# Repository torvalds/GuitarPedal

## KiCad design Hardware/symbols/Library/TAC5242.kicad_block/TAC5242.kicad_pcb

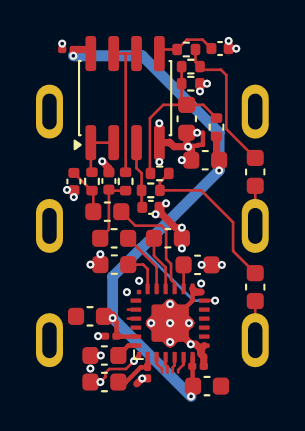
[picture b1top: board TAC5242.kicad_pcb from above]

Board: 4 copper layers, 32 parts (1 on the bottom side), 20 nets.

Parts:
C903, C904, C906, C907, C910, C911, C912, C922, C923: 2.2uF; C_0603_1608Metric
C905, C918, C919, C921: 0.1uF; C_0201_0603Metric
C908, C913: 150pF; C_0402_1005Metric
C909, C914: 2.2nF; C_0402_1005Metric
C915, C916, C917, C920: 10uF; C_0603_1608Metric
J901: AudioJack3_SwitchTR; NRJ6HM-1-PRE
R901, R902, R907, R908: 100R; R_0402_1005Metric
R903, R904, R905, R906: 1MEG; R_0402_1005Metric
U902: OPA2365AIDR; SOIC-8_3.9x4.9mm_P1.27mm
U903: TAC5242

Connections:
+3.3VA: C905.2, C915.1, C916.1, C917.1, C918.1, C919.1, R904.1, U902.8 (V+), U903.6 (IOVDD), U903.12 (MD5), U903.23 (AVDD)
/DREG: C920.1, C921.1, U903.1 (DREG)
/IN1M: C903.2, U903.16 (IN1M)
/IN1P: C907.2, U903.15 (IN1P)
/IN2M: C904.2, U903.18 (IN2M)
/IN2P: C912.2, U903.17 (IN2P)
/IN^{LEFT}: C906.1, J901.T
/IN^{RIGHT}: C911.1, J901.R
/MICBIAS: C923.1, U903.14 (MICBIAS)
/VREF: C922.1, U903.24 (VREF)
GND: C903.1, C904.1, C905.1, C908.2, C909.1, C910.1, C913.2, C914.1, C915.2, C916.2, C917.2, C918.2, C919.2, C920.2, C921.2, C922.2, C923.2, J901.RN, J901.S, J901.TN, R905.2, U902.4 (V-), U903.7 (MD1), U903.8 (MD2), U903.9 (MD3), U903.10 (MD4), U903.13 (MD0), U903.A1 (GND), U903.A2 (GND), U903.A3 (GND), U903.A4 (GND), U903.PAD (GND)
unnamed: C906.2, R901.1, R903.2
unnamed: C907.1, C909.2, R902.2
unnamed: C910.2, R903.1, R904.2, R905.1, R906.2
unnamed: C911.2, R906.1, R907.1
unnamed: C912.1, C914.2, R908.2
unnamed: C908.1, R901.2, U902.3 (+)
unnamed: R902.1, U902.1, U902.2 (-)
unnamed: C913.1, R907.2, U902.5 (+)
unnamed: R908.1, U902.6 (-), U902.7

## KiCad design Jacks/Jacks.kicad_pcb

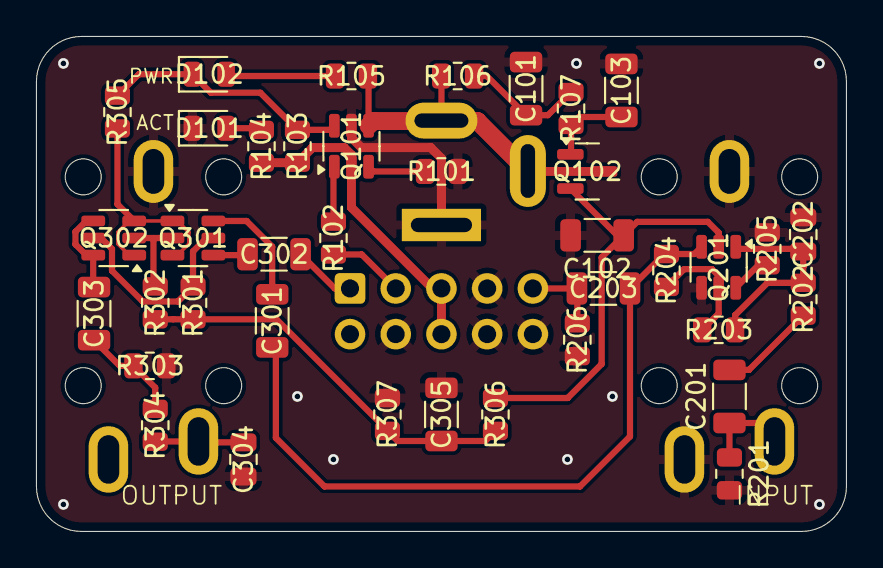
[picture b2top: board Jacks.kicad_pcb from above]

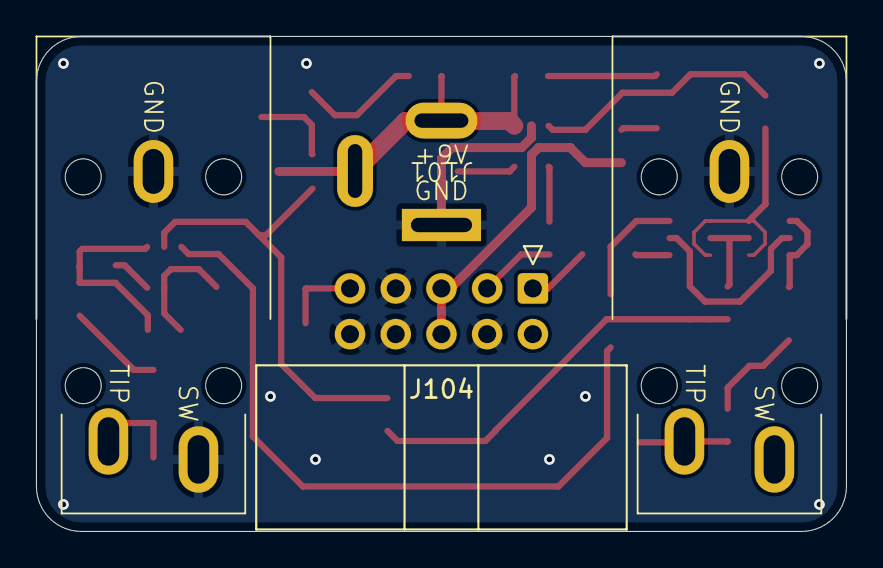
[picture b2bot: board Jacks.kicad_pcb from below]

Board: 2 copper layers, 45.0 x 27.5 mm, 44 parts (4 on the bottom side), 29 nets.

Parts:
Box101: 125B
Box102: 1590B
C101, C102, C103, C305: 10uF; C_1206_3216Metric
C201, C203: 4.7uF; C_1206_3216Metric
C202: 150pF; C_0805_2012Metric
C301, C302, C303: 1uF; C_1206_3216Metric
C304: 220pF; C_0805_2012Metric
D101, D102: LED; LED_0805_2012Metric
J101: Barrel_Jack_Switch; Wurth WR-DC 2.1mm Power Jack
J102, J103: AudioJack2_Ground; CK-6.35
J104: Conn_02x05_Odd_Even; IDC-Header_2x05_P2.54mm_Horizontal
Q101, Q301, Q302: DMC3071LVT; TSOT-23-6
Q102: BC846; SOT-23
Q201: LS844; SOT-23-6
R101, R102, R103: 100k; R_0805_2012Metric
R104, R105, R106, R107, R304: 2k2; R_0805_2012Metric
R201, R203, R206, R301, R302, R303: 1MEG; R_0805_2012Metric
R202: 1k; R_0805_2012Metric
R204, R205: 1k5; R_0805_2012Metric
R305: 10MEG; R_0805_2012Metric
R306, R307: 4k7; R_0805_2012Metric

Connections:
+VA: C102.1, Q102.2 (E), Q201.2 (D), R306.2
BUFFERED: C203.1, C301.1, Q201.3 (S), R204.1
GATE: Q301.1 (G), Q301.3 (G), Q302.1 (G), Q302.3 (G), R305.2
GND: C101.2, C102.2, C103.2, C202.2, C304.2, C305.1, D101.1 (K), J101.1, J102.G, J102.S, J103.G, J104.4, J104.7, J104.8, J104.10, Q101.5 (S), Q201.4 (G), R101.2, R201.2, R205.2, R206.2, R303.1, R307.1
IN^{CONN}: C201.1, J102.T, R201.1
IN^{EFF}: C203.2, J104.9, R206.1
unnamed: C101.1, R106.2, R107.1
unnamed: C201.2, R202.1
unnamed: C303.2, R303.2, R304.1
unnamed: D101.2 (A), R104.2
unnamed: D102.2 (A), R105.2
unnamed: Q101.1 (G), R102.2
unnamed: Q101.3 (G), R101.1
unnamed: C103.1, Q102.1 (B), R107.2
unnamed: C202.1, Q201.1 (G), R202.2, R203.1
unnamed: Q201.5 (D), R203.2, R204.2
unnamed: Q201.6 (S), R205.1
unnamed: C301.2, Q301.6 (D)
unnamed: Q301.5 (S), Q302.5 (S), R301.1
unnamed: C302.2, Q301.4 (D)
unnamed: Q301.2 (S), Q302.2 (S), R302.2
unnamed: C303.1, Q302.4 (D), Q302.6 (D)
ON_LOW: D102.1 (K), Q101.6 (D), R103.2, R305.1
ON_OFF: J104.3, R102.1
OUT^{CONN}: C304.1, J103.T, R304.2
OUT^{EFF}: C302.1, J104.1
PWRIN: J101.2, J101.3, Q101.4 (D), Q102.3 (C), R105.1, R106.1
VBIAS: C305.2, R301.2, R302.1, R306.1, R307.2
VIN: J104.5, J104.6, Q101.2 (S), R103.1, R104.1

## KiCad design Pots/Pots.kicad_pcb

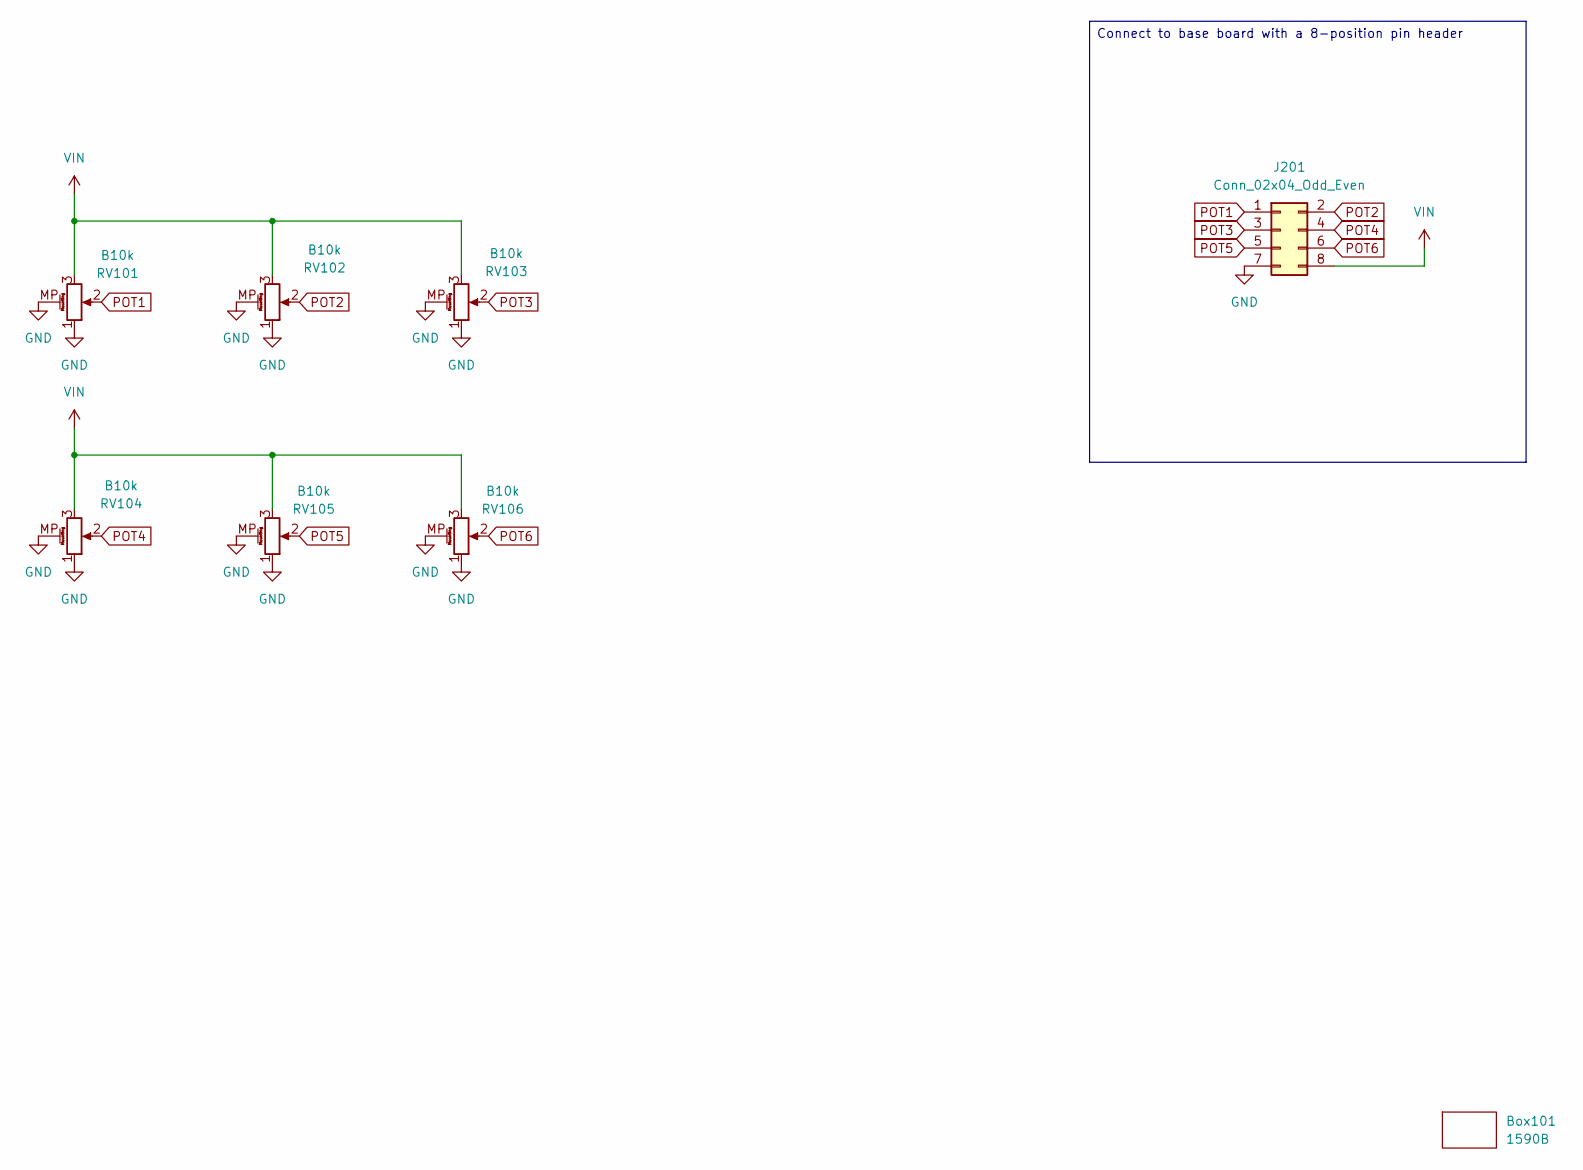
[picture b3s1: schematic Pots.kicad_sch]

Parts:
Box101: 1590B
J201: Conn_02x04_Odd_Even; PinSocket_2x04_P2.54mm_Vertical
RV101, RV102, RV103, RV104, RV105, RV106: B10k; Potentiometer_9mm_MP_Low_profile

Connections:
GND: J201.7, RV101.1, RV101.MP (MountPin), RV102.1, RV102.MP (MountPin), RV103.1, RV103.MP (MountPin), RV104.1, RV104.MP (MountPin), RV105.1, RV105.MP (MountPin), RV106.1, RV106.MP (MountPin)
POT1: J201.1, RV101.2
POT2: J201.2, RV102.2
POT3: J201.3, RV103.2
POT4: J201.4, RV104.2
POT5: J201.5, RV105.2
POT6: J201.6, RV106.2
VIN: J201.8, RV101.3, RV102.3, RV103.3, RV104.3, RV105.3, RV106.3

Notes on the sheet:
Connect to base board with a 8-position pin header

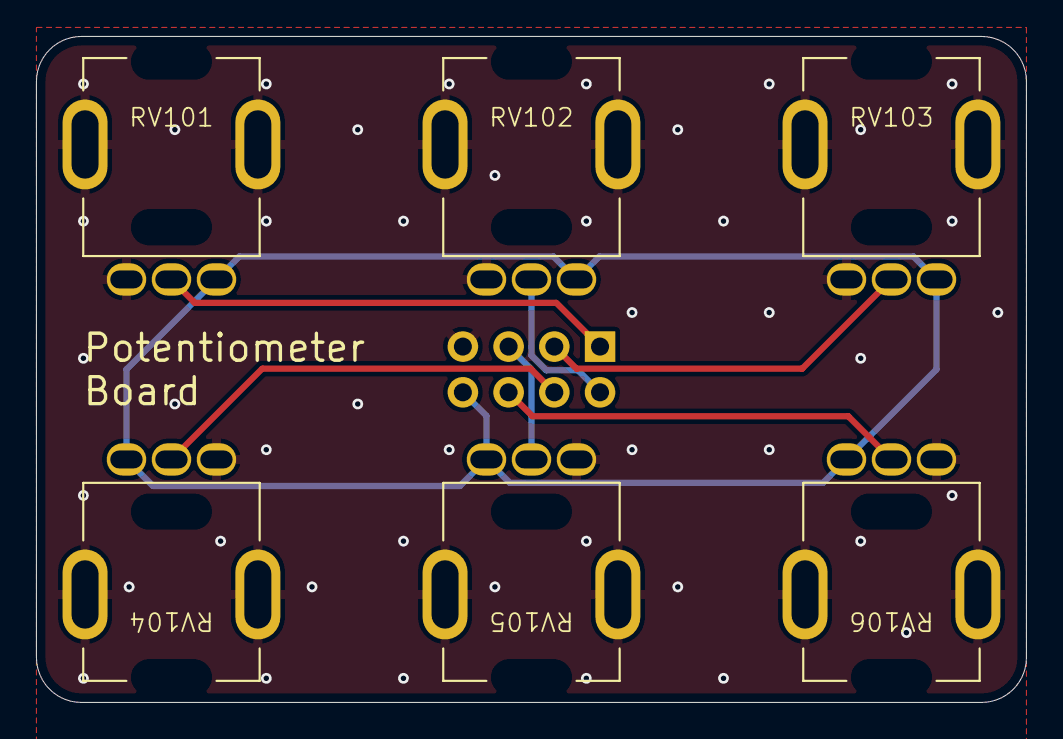
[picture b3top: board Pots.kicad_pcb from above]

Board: 2 copper layers, 55.0 x 37.0 mm, 8 parts (1 on the bottom side), 8 nets.

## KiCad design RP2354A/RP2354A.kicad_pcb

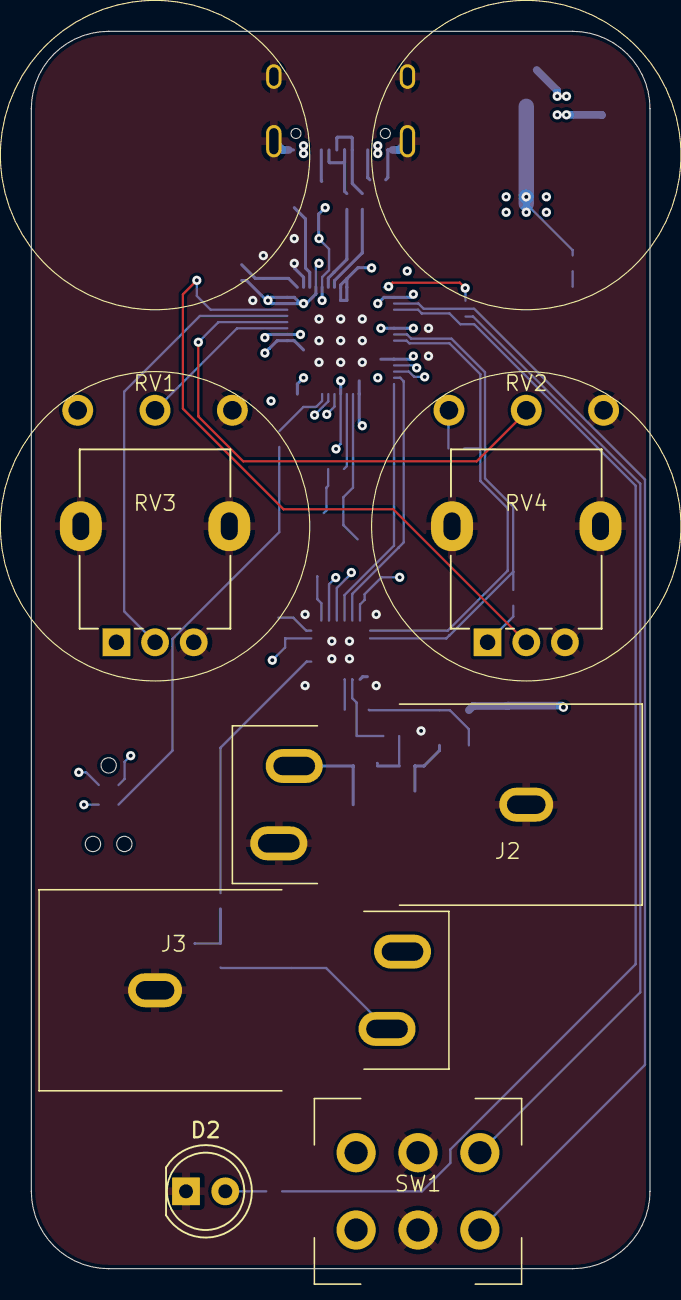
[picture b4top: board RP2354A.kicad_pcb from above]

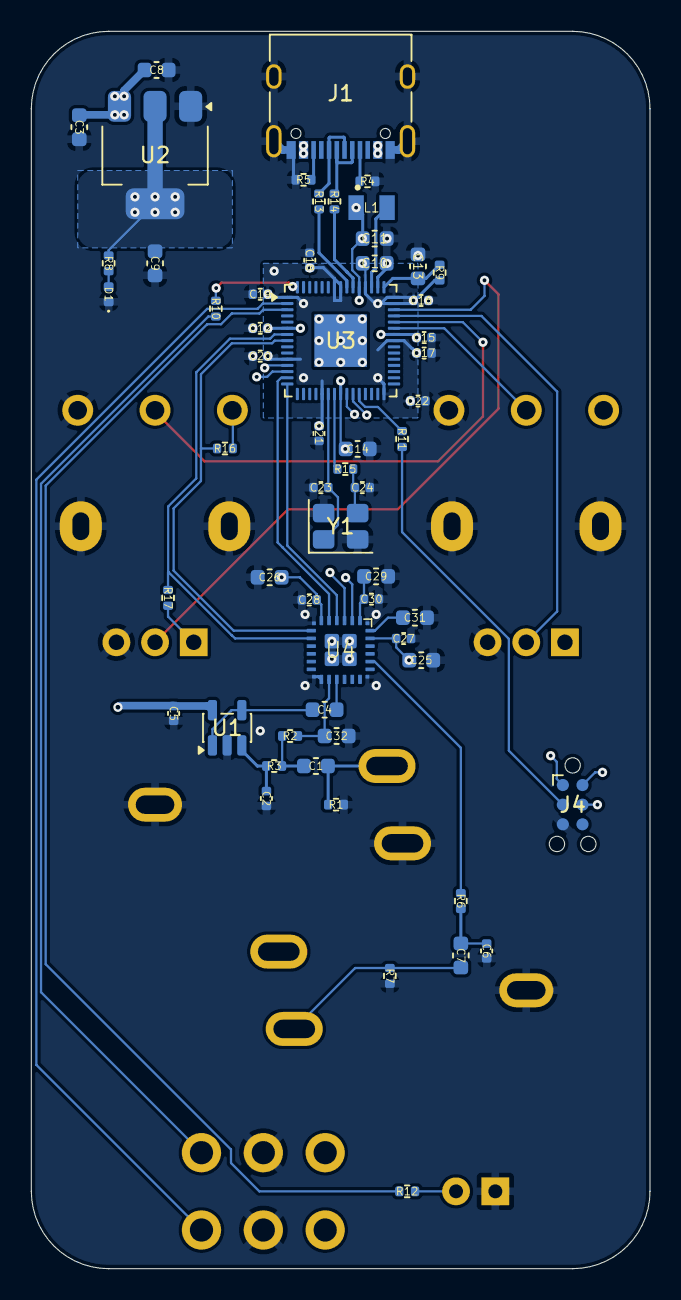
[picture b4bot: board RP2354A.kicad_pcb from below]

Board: 6 copper layers, 40.0 x 80.0 mm, 66 parts (58 on the bottom side), 46 nets.

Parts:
C1, C4, C7, C31, C32: 1uF; C_0603_1608Metric
C2, C6: 150pF; C_0402_1005Metric
C3, C8, C9, C25, C26, C29: 10uF; C_0603_1608Metric
C5, C12, C15, C16, C17, C18, C19, C20, C21, C22, C27, C28, C30: 0.1uF; C_0402_1005Metric
C10, C11, C13, C14: 4.7uF; C_0603_1608Metric
C23, C24: 15pF; C_0402_1005Metric
D1: LED; LED_0402_1005Metric
D2: LED; LED_D5.0mm
J1: TYPE-C16PIN; USB_C_Receptacle_XKB_U262-16XN-4BVC11
J2, J3: AudioJack2_SwitchT; CK-6.35-no-NPTH
J4: TC2030-NL; Tag-Connect_TC2030-IDC-NL_2x03_P1.27mm_Vertical
L1: 3.3uH; AOTA-B2016
R1, R2, R7: 1MEG; R_0402_1005Metric
R3, R6, R8, R10, R11, R12, R15: 1k; R_0402_1005Metric
R4, R5, R16, R17: 5k1; R_0402_1005Metric
R9, R13, R14: 33R; R_0402_1005Metric
RV1, RV2: 10k; Potentiometer-Basic
RV3, RV4: 10k; Potentiometer_9mm_MP
SW1: SW_Push_DPDT; FS5700DPMT2B2M2QE
U1: OPA365xxDBV; SOT-23-5
U2: NCP1117-3.3_SOT223; SOT-223-3_TabPin2
U3: RP2354A; QFN-60-1EP_7x7mm_P0.4mm_EP3.4x3.4mm
U4: TAC5112
Y1: ABM8-272-T3; Crystal_SMD_3225-4Pin_3.2x2.5mm

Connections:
+1V1: C11.1, C12.1, C14.1, C15.1, L1.1, U3.6 (DVDD), U3.23 (DVDD), U3.39 (DVDD), U3.50 (VREG_FB)
+3V3: C9.1, C10.1, C16.1, C17.1, C18.1, C19.1, C20.1, C21.1, C22.1, C25.1, C26.1, C27.1, C28.1, J4.1 (VCC), R8.1, R9.1, R16.1, R17.1, RV1.1, RV2.1, RV3.1, RV4.1, U2.2 (VO), U3.1 (IOVDD), U3.11 (IOVDD), U3.20 (IOVDD), U3.30 (IOVDD), U3.38 (IOVDD), U3.44 (ADC_AVDD), U3.45 (IOVDD), U3.49 (VREG_VIN), U3.53 (USB_OTP_VDD), U3.54 (QSPI_IOVDD), U4.6 (IOVDD), U4.23 (AVDD)
/RPi/BOOTSEL: R10.1, SW1.3 (C)
/RPi/LED: R12.2, U3.3 (GPIO1)
/RPi/NRST: J4.3 (~RESET), R11.1
/RPi/STOMP: SW1.6 (C), U3.2 (GPIO0)
/RPi/VREG_AVDD: C13.1, R9.2, U3.46 (VREG_AVDD)
/RPi/VREG_LX: L1.2, U3.48 (VREG_LX)
/RPi/XIN: C23.1, U3.21 (XIN), Y1.1
/RPi/XOUT: R15.1, U3.22 (XOUT)
BCLK: U3.12 (GPIO8), U4.2 (BCLK)
DIN: U3.14 (GPIO10), U4.5 (DIN)
DOUT: U3.15 (GPIO11), U4.4 (DOUT)
DREG: C29.1, C30.1, U4.1 (DREG)
FSYNC: U3.13 (GPIO9), U4.3 (FSYNC)
GND: C2.2, C3.1, C5.1, C6.1, C8.2, C9.2, C10.2, C11.2, C12.2, C13.2, C14.2, C15.2, C16.2, C17.2, C18.2, C19.2, C20.2, C21.2, C22.2, C23.2, C24.2, C25.2, C26.2, C27.2, C28.2, C29.2, C30.2, C31.2, C32.2, D1.1 (K), D2.1 (K), J1.A1 (GND), J1.A12 (GND), J1.B1 (GND), J1.B12 (GND), J1.S1 (SHIELD), J2.S, J2.TN, J3.S, J4.5 (GND), R1.2, R4.2, R5.2, R7.2, RV1.3, RV2.3, RV3.3, RV3.MP (MountPin), RV4.3, RV4.MP (MountPin), SW1.2 (B), SW1.5 (B), U1.2 (V-), U2.1 (GND), U3.47 (VREG_PGND), U3.61 (GND), U4.13 (ADDR), U4.A1 (GND), U4.A2 (GND), U4.A3 (GND), U4.A4 (GND), U4.PAD (GND), Y1.2, Y1.4
IN^{CONN}: C1.1, J2.T, R1.1
IN^{EFF}: C4.2, U4.15 (IN1P)
unnamed: C1.2, R2.2, R3.1
unnamed: C6.2, C7.1, R6.2
unnamed: C24.1, R15.2, Y1.3
unnamed: D1.2 (A), R8.2
unnamed: D2.2 (A), R12.1
unnamed: J1.A5 (CC1), R4.1
unnamed: J1.B5 (CC2), R5.1
unnamed: J4.4 (SWCLK), U3.24 (SWCLK)
unnamed: J4.2 (SWDIO), U3.25 (SWD)
unnamed: C2.1, R3.2, U1.3 (+)
unnamed: C4.1, U1.1, U1.4 (-)
unnamed: R10.2, U3.60 (QSPI_SS)
unnamed: R11.2, U3.26 (RUN)
unnamed: R14.1, U3.51 (USB_DM)
unnamed: R13.1, U3.52 (USB_DP)
OUT^{CONN}: C7.2, J3.T, R7.1
OUT^{EFF}: R6.1, U4.20 (OUT1P)
POT1: RV1.2, U3.40 (GPIO26_ADC0)
POT2: RV2.2, U3.41 (GPIO27_ADC1)
POT3: RV3.2, U3.42 (GPIO28_ADC2)
POT4: RV4.2, U3.43 (GPIO29_ADC3)
SCL: R16.2, U3.8 (GPIO5), U4.7 (SCL)
SDA: R17.2, U3.7 (GPIO4), U4.8 (SDA)
USB_D+: J1.A6 (D+), J1.B6 (D+), R13.2
USB_D-: J1.A7 (D-), J1.B7 (D-), R14.2
VBIAS: C32.1, R2.1, U4.14 (MICBIAS)
VBUS: C3.2, C5.2, C8.1, J1.A4 (VBUS), J1.A9 (VBUS), J1.B4 (VBUS), J1.B9 (VBUS), U1.5 (V+), U2.3 (VI)
VREF: C31.1, U4.24 (VREF)

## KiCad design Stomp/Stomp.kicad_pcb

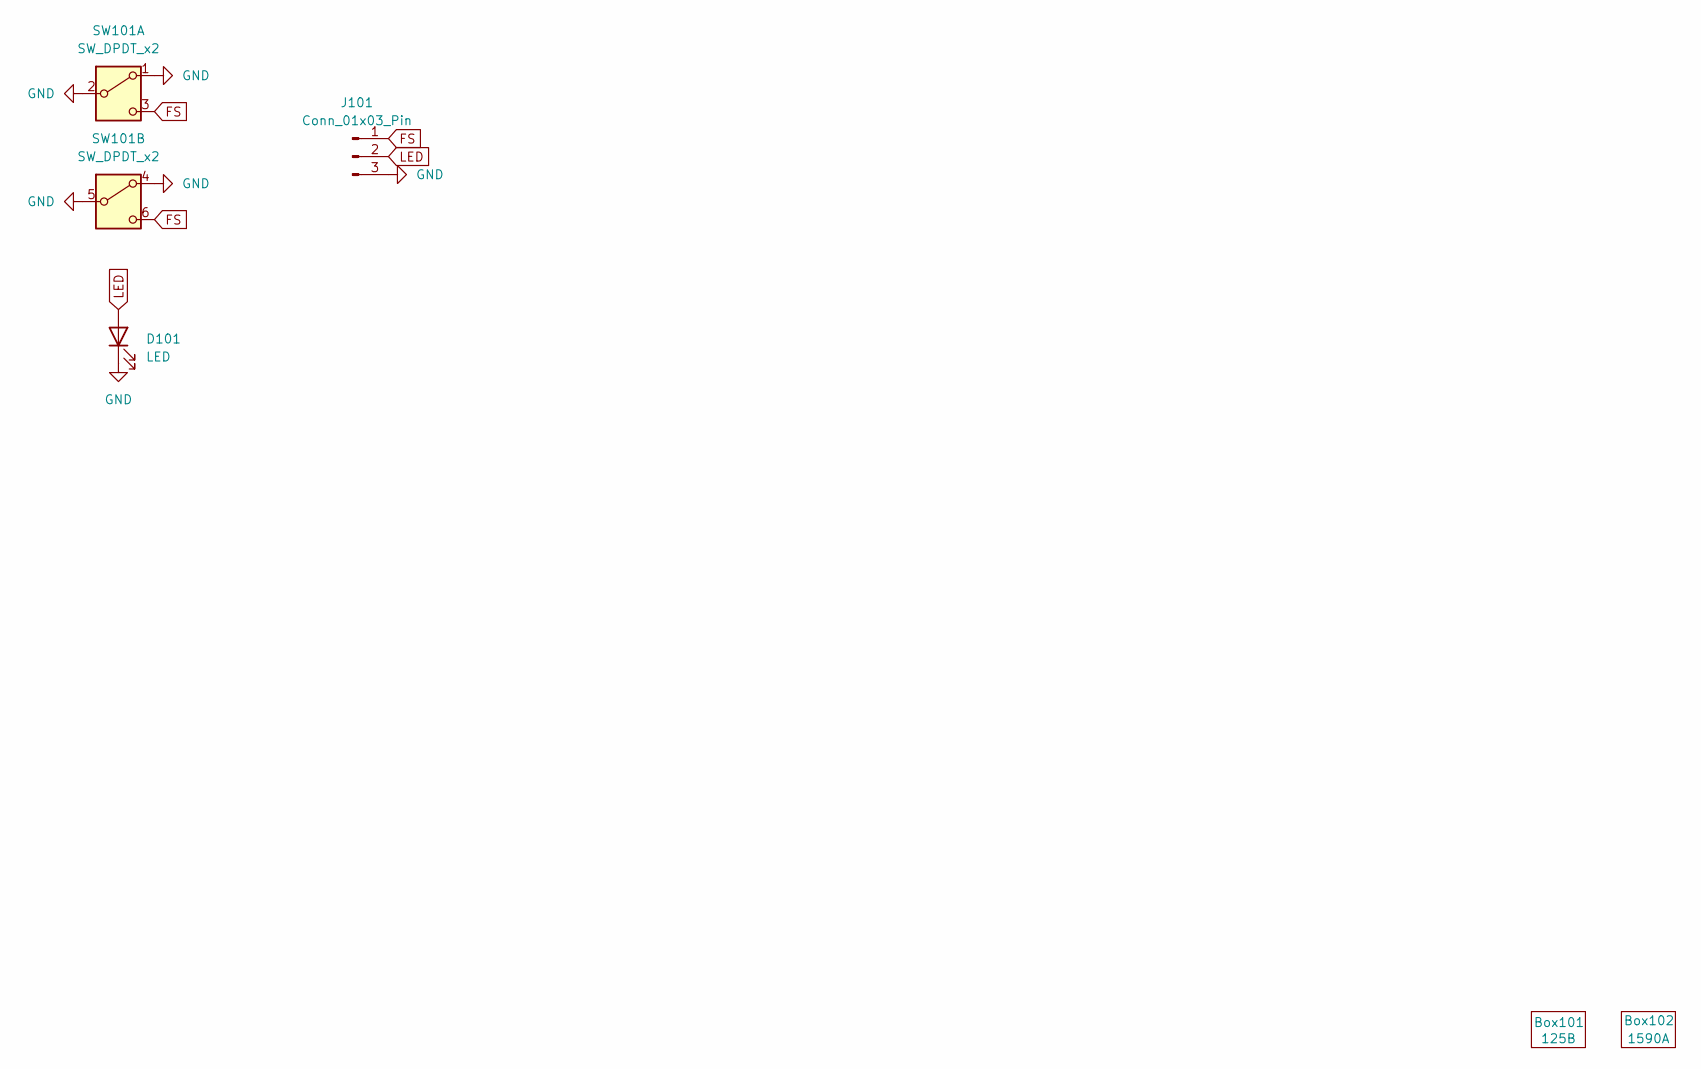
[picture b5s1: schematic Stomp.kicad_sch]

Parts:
Box101: 125B
Box102: 1590A
D101: LED; LED_D5.0mm
J101: Conn_01x03_Pin; JST_ZH_B3B-ZR_1x03_P1.50mm_Vertical
SW101: SW_DPDT_x2; FS5700DPMT2B2M2QE

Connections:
FS: J101.1, SW101.3 (C), SW101.6 (C)
GND: D101.1 (K), J101.3, SW101.1 (A), SW101.2 (B), SW101.4 (A), SW101.5 (B)
LED: D101.2 (A), J101.2

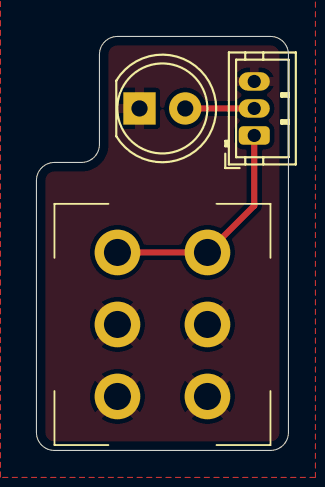
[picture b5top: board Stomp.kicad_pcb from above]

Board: 2 copper layers, 14.0 x 23.0 mm, 5 parts (0 on the bottom side), 3 nets.
